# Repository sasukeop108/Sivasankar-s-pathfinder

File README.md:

# Sivasankar-s-pathfinder
This is a pathfinder project which i made by following the pathfinder tutorial in stasis.

# JLCPCB BOM

# robu bom

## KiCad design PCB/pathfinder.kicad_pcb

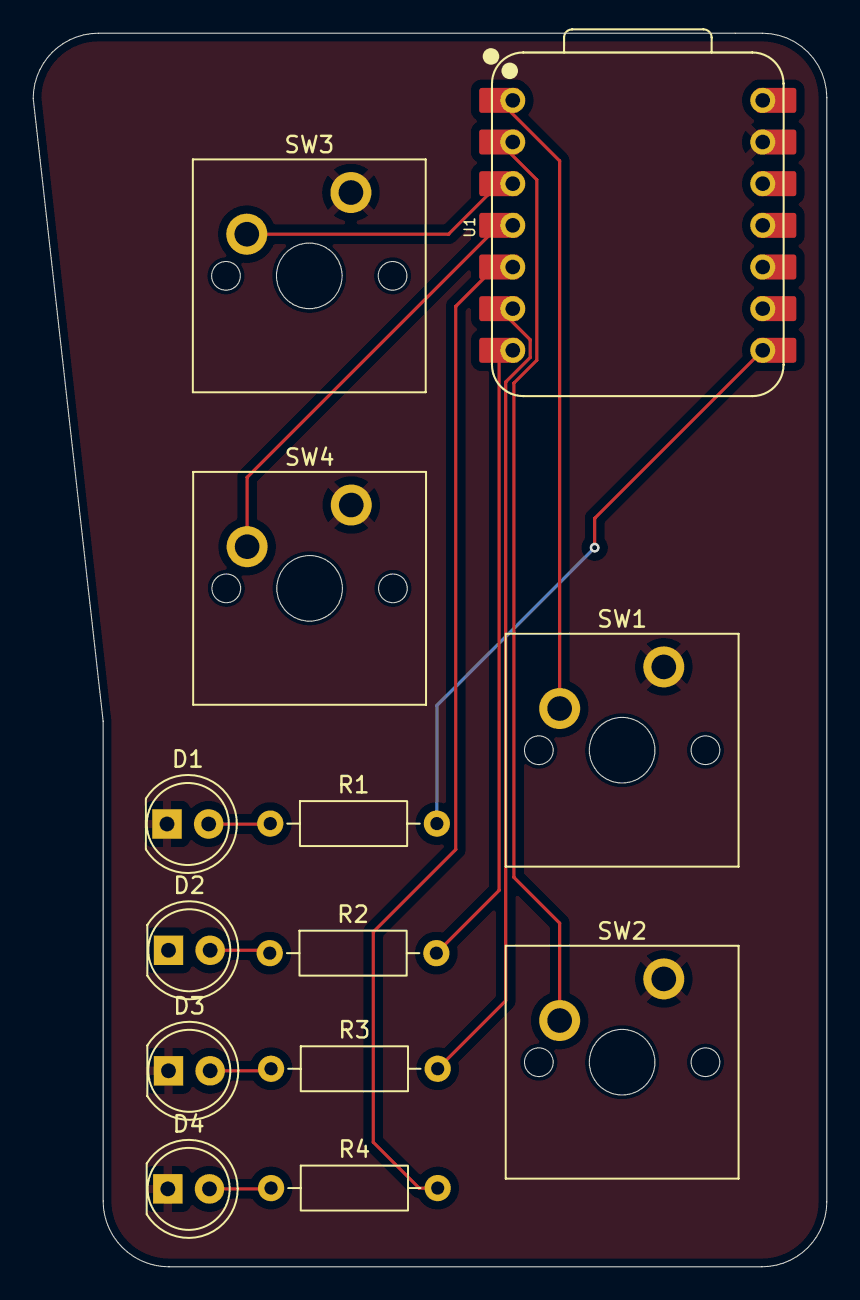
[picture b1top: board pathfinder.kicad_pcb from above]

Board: 2 copper layers, 48.4 x 75.2 mm, 13 parts (0 on the bottom side), 13 nets.

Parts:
D1, D2, D3, D4: LED; LED_D5.0mm
R1, R2, R3, R4: R; R_Axial_DIN0207_L6.3mm_D2.5mm_P10.16mm_Horizontal
SW1, SW2, SW3, SW4: SW_Push; MX_PCB_1.00u
U1: XIAO-RP2040-DIP; XIAO-RP2040-DIP1

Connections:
GND: D1.1 (K), D3.1 (K), D4.1 (K), SW1.2, SW2.2, SW3.2, SW4.2, U1.13 (GND)
GPIO0: SW1.1, U1.1 (P26_A0_D0)
GPIO1: SW2.1, U1.2 (P27_A1_D1)
GPIO2: SW3.1, U1.3 (P28_A2_D2)
GPIO3: SW4.1, U1.4 (P29_A3_D3)
GPIO4: R4.2, U1.5 (P6_SDA_D4)
GPIO5: R3.2, U1.6 (P7_SCL_D5)
GPIO6: R2.2, U1.7 (P0_D6_TX)
GPIO7: R1.2, U1.8 (P1_D7_RX)
unnamed: D1.2 (A), R1.1
unnamed: D2.2 (A), R2.1
unnamed: D3.2 (A), R3.1
unnamed: D4.2 (A), R4.1

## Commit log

2026-04-05 Create a
2026-04-05 Create assets
2026-04-05 Create PCB
